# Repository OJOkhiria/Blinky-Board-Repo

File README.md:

# Blinky-Board-Repo
This is a starter project that uses a 555 timer in astable mode and a CD4017 IO expander to create a heart-shaped light-up board (with an optional Iron Man reference). On the 555 timer, astable mode produces a continuous oscillating signal. In this configuration, the 555 timer repeatedly toggles its output between high and low states, with both the frequency and pulse width adjustable. Essentially, this mode makes the timer act like a blinking light. It keeps switching ON and OFF, without needing you to press anything, making it the perfect choice for a lights that blink on their own. It was made entirely with KiCad. PCB was custom-printed and hand-soldered using the resulting Gerber files. Full BOM is listed below and attached.

[Blinky Board .csv](https://github.com/user-attachments/files/27324070/Blinky.Board.csv)
Reference	Qty	Value	DNP	Exclude from BOM	Exclude from Board	Footprint	Datasheet
C1	1	0.01 uF				Capacitor_THT:CP_Radial_D5.0mm_P2.00mm	
C2	1	1 uF				Capacitor_THT:C_Disc_D7.5mm_W2.5mm_P5.00mm	
D1LED1,D2LED1,D5LED1,D6LED1,D7LED1,D8LED1,D9LED1,D10LED1,D11LED1,D12LED1	10	LED				LED_THT:LED_D3.0mm	
J1	1	Conn_01x02_Socket				Connector_PinHeader_2.54mm:PinHeader_1x02_P2.54mm_Vertical	
J2	1	Conn_01x01_Socket				Connector_PinHeader_2.54mm:PinHeader_1x01_P2.54mm_Vertical	
R1	1	1k				Resistor_THT:R_Axial_DIN0207_L6.3mm_D2.5mm_P7.62mm_Horizontal	
R2	1	470				Resistor_THT:R_Axial_DIN0207_L6.3mm_D2.5mm_P7.62mm_Horizontal	
RV1	1	50k				Potentiometer_THT:Potentiometer_Vishay_T93YA_Vertical	
U1	1	NE555P				Package_DIP:DIP-8_W7.62mm	http://www.ti.com/lit/ds/symlink/ne555.pdf
U2	1	4017				CMOS Decade Counter with 10 Decoded Outputs 16-PDIP -55 to 125:N16	http://www.intersil.com/content/dam/Intersil/documents/cd40/cd4017bms-22bms.pdf

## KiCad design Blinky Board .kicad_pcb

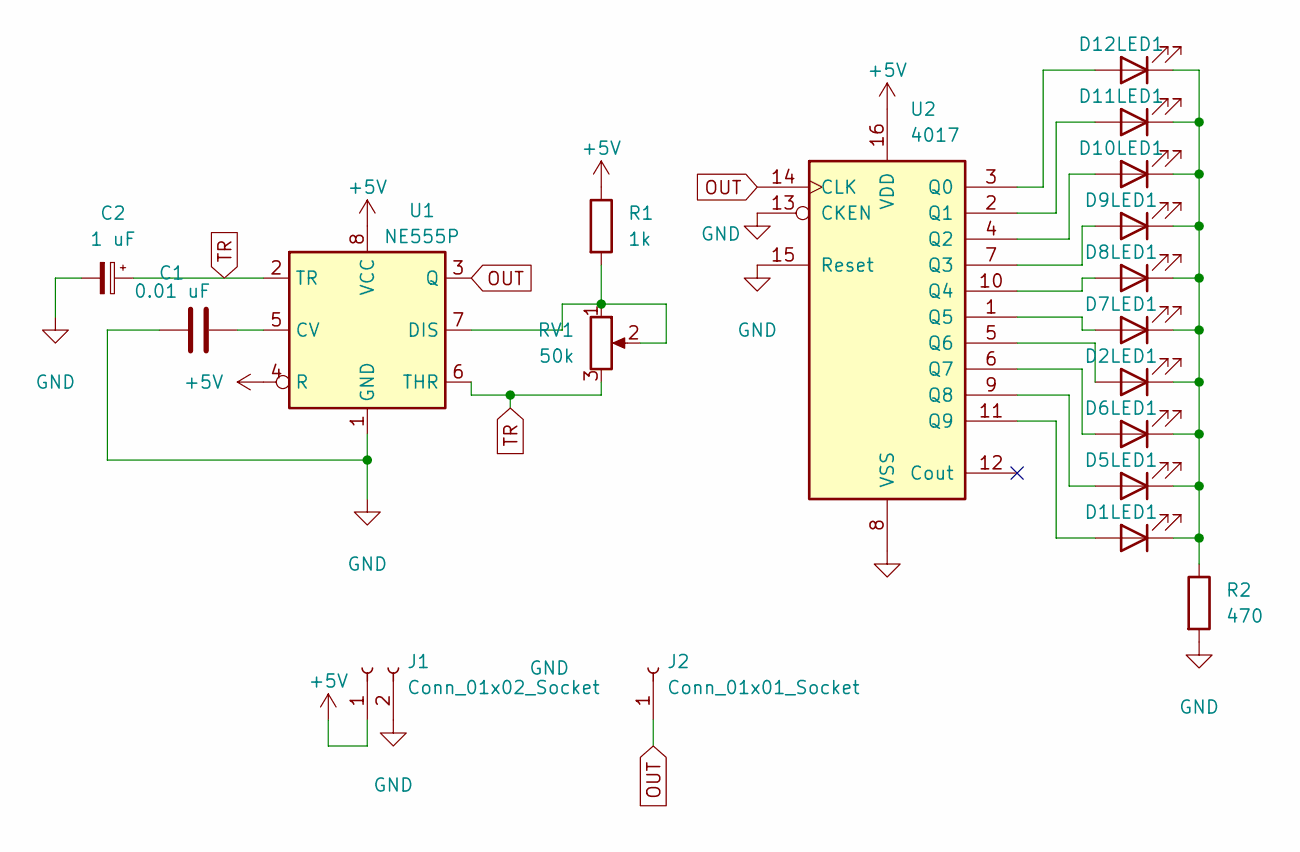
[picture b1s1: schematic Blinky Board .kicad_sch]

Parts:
C1: 0.01 uF; CP_Radial_D5.0mm_P2.00mm
C2: 1 uF; C_Disc_D7.5mm_W2.5mm_P5.00mm
D1LED1, D2LED1, D5LED1, D6LED1, D7LED1, D8LED1, D9LED1, D10LED1, D11LED1, D12LED1: LED; LED_D3.0mm
J1: Conn_01x02_Socket; PinHeader_1x02_P2.54mm_Vertical
J2: Conn_01x01_Socket; PinHeader_1x01_P2.54mm_Vertical
R1: 1k; R_Axial_DIN0207_L6.3mm_D2.5mm_P7.62mm_Horizontal
R2: 470; R_Axial_DIN0207_L6.3mm_D2.5mm_P7.62mm_Horizontal
RV1: 50k; Potentiometer_Vishay_T93YA_Vertical
U1: NE555P; DIP-8_W7.62mm
U2: 4017; N16

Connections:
+5V: J1.1, R1.1, U1.4 (R), U1.8 (VCC), U2.16 (VDD)
GND: C1.1, C2.2, J1.2, R2.2, U1.1 (GND), U2.8 (VSS), U2.13 (CKEN), U2.15 (Reset)
unnamed: D1LED1.2 (A), U2.11 (Q9)
unnamed: D2LED1.2 (A), U2.5 (Q6)
unnamed: D5LED1.2 (A), U2.9 (Q8)
unnamed: D6LED1.2 (A), U2.6 (Q7)
unnamed: D7LED1.2 (A), U2.1 (Q5)
unnamed: D8LED1.2 (A), U2.10 (Q4)
unnamed: D9LED1.2 (A), U2.7 (Q3)
unnamed: D10LED1.2 (A), U2.4 (Q2)
unnamed: D1LED1.1 (K), D2LED1.1 (K), D5LED1.1 (K), D6LED1.1 (K), D7LED1.1 (K), D8LED1.1 (K), D9LED1.1 (K), D10LED1.1 (K), D11LED1.1 (K), D12LED1.1 (K), R2.1
unnamed: D11LED1.2 (A), U2.2 (Q1)
unnamed: D12LED1.2 (A), U2.3 (Q0)
unnamed: C1.2, U1.5 (CV)
unnamed: R1.2, RV1.1, RV1.2, U1.7 (DIS)
OUT: J2.1 (Pin_1_1), U1.3 (Q), U2.14 (CLK)
TR: C2.1, RV1.3, U1.2 (TR), U1.6 (THR)

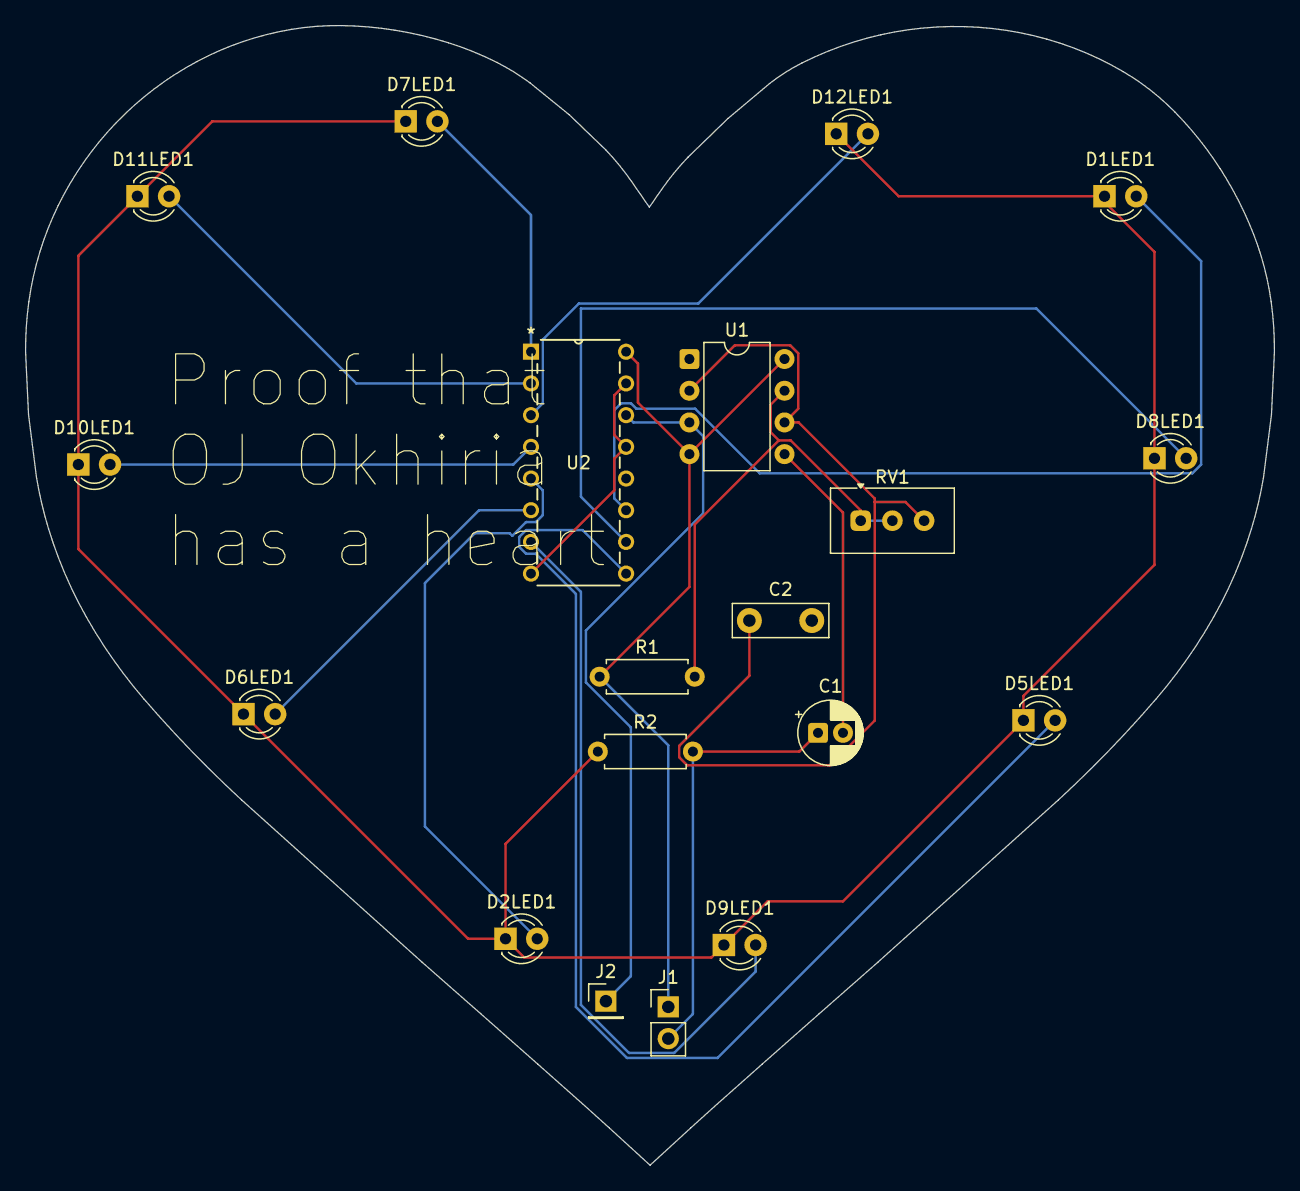
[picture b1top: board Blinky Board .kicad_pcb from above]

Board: 2 copper layers, 100.1 x 91.3 mm, 19 parts (0 on the bottom side), 17 nets.
